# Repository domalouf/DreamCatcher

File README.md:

# DreamCatcher
 A react native mobile app for the DreamCatcher sleep mask

- `DreamCatcherAppNew/` - the app
- `arduino/` - mask firmware
- `hardware/` - PCB design for the mask ([details](hardware/README.md))

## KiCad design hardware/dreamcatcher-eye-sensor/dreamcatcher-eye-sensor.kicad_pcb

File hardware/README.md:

# DreamCatcher hardware

Two small boards that replace the ESP32 dev board and the QTR-1A breakout in the mask:

| Board | Size | What's on it |
| --- | --- | --- |
| [Main board](dreamcatcher-main) | 50 x 18 mm, 4 layers, parts on one side | ESP32-C3 module, USB-C charging and flashing, LiPo charger, 3.3 V regulator, accelerometer, two eye sensor connectors |
| [Eye sensor board](dreamcatcher-eye-sensor) (one per eye) | 8 x 9.5 mm, 2 layers | IR reflectance sensor and a red cue LED |

The main board sits on the forehead or temple. Each eye sensor board sits in front of an
eye and connects to the main board with a thin four-wire cable, so nothing bulky
presses on the eye.

**This design has not been built yet.** It passes an automated test suite (see
[What has been checked](#what-has-been-checked)), but no board has been manufactured or
powered. Read [Before you order](#before-you-order) first.

## How it works

```mermaid
flowchart LR
    USB[USB-C] --> CHG[MCP73831 charger<br/>100 mA]
    USB --> PATH[Power path<br/>Q1 + D1]
    CHG --> BAT[LiPo cell]
    BAT --> PATH
    PATH --> LDO[XC6220<br/>3.3 V]
    LDO --> MCU[ESP32-C3-MINI-1]
    USB <-- data --> MCU
    MCU -- I2C --> ACC[LIS2DH12<br/>accelerometer]
    MCU -- sensor power switch --> EYES
    MCU -- cue LED drive --> EYES[Left and right<br/>eye sensor boards]
    EYES -- analog --> MCU
    BAT -- divider --> MCU
```

- **Eye sensors.** Each eye board carries a QRE1113GR, the same sensor as on the QTR-1A
  you use now, wired the same way: a 220 Ω resistor for the IR LED and a 47 kΩ pull-up
  on the phototransistor. Those resistors are on the main board, so the eye board holds
  only the sensor and the cue LED. Q2 switches power to both sensors, so they draw
  nothing between readings.
- **Accelerometer.** A LIS2DH12 detects head and body movement directly, instead of
  inferring it from the IR signal. Its interrupt pin can wake the chip from deep sleep.
- **Power.** USB-C charges the cell at 100 mA. On USB the board runs from USB and the
  cell only charges (Q1 and D1), so charging finishes properly. The regulator draws
  about 8 µA itself.
- **USB.** The ESP32-C3's built-in USB serial/JTAG is wired to the connector, so the
  board is flashed over USB-C with no extra chip.

### Pin map

| ESP32-C3 pin | Net | Use |
| --- | --- | --- |
| GPIO0 (ADC1_CH0) | `EYE_L_OUT` | Left eye sensor reading |
| GPIO1 (ADC1_CH1) | `EYE_R_OUT` | Right eye sensor reading |
| GPIO2 | `SENS_EN_N` | Eye sensor power, **low = on** |
| GPIO3 (ADC1_CH3) | `VBAT_SENSE` | Battery voltage / 2 |
| GPIO4 | `ACC_INT1` | Accelerometer interrupt (can wake from deep sleep) |
| GPIO5 | `CUE_L` | Left cue LED, high = on |
| GPIO6 | `CUE_R` | Right cue LED, high = on |
| GPIO7 | `LED_STAT` | Green status LED on the main board, high = on |
| GPIO8 | `I2C_SDA` | Accelerometer (address 0x19) |
| GPIO10 | `I2C_SCL` | Accelerometer |
| GPIO9 | `BOOT` | BOOT pad |
| GPIO18 / GPIO19 | `USB_DM` / `USB_DP` | USB |
| GPIO20 / GPIO21 | `UART_RX` / `UART_TX` | Debug pads |

### Eye sensor cable

Both ends use the same order. The main board has a JST SH 4-pin socket (1 mm pitch) for
each eye; the eye board has four plated holes to solder the wires into.

| Pin | Signal |
| --- | --- |
| 1 | Cue LED anode |
| 2 | Ground |
| 3 | Phototransistor output |
| 4 | IR LED anode |

A ready-made "JST SH 4-pin to bare wire" cable works: plug one end into the main board
and solder the other to the eye board. These are the same plugs as Qwiic / STEMMA QT
cables, but the signals are not I2C, so don't plug a Qwiic device in.

## Before you order

1. **Pick the battery.** The charger is set to 100 mA (R3 = 10 kΩ), which suits a cell
   of 100 mAh or more. For another charge current use R3 = 1000 / amps. Use a cell with
   its own protection circuit (most pouch cells with leads have one); the board has no
   under-voltage cut-off of its own. The leads solder to the two pads marked + and −.
   There is no reverse-polarity protection, so check the lead colours against the
   markings before soldering.
2. **Look the boards over in KiCad.** The tracks were placed by a script, not by hand.
   They pass the design rule check, but they are not pretty, and a second pair of eyes
   on a first board is always worth it. The main board also has spare room: someone
   laying it out by hand could bring it down to roughly 45 x 18 mm.
3. **Check the parts in JLCPCB's parts list.** Stock changes daily. Things I noticed:
   - QRE1113GR (C232862) had low stock and one listing calls it not recommended for new
     designs. If it's unavailable, leave it off the order and solder sensors from
     Digi-Key or Mouser yourself.
   - ESP32-C3-MINI-1-N4 (C2838502) may be replaced by the newer ESP32-C3-MINI-1-N4X,
     which has the same footprint.
   - I could not confirm the green LED's part number (C72043).
4. **Check part rotation in JLCPCB's placement preview.** Their rotation convention
   differs from KiCad's for some packages (SOT-23, the USB connector, LEDs). Their
   preview shows each part on its pads; fix any that look turned.

### Ordering from JLCPCB

Each board folder has a `fab/` folder with what the order form asks for:

| File | Upload as |
| --- | --- |
| `*-gerbers.zip` | Gerber file |
| `*-bom.csv` | BOM (assembly step) |
| `*-cpl.csv` | CPL / pick-and-place file (assembly step) |

Settings that differ from the defaults:

| | Main board | Eye sensor board |
| --- | --- | --- |
| Layers | 4 | 2 |
| Thickness | 0.8 mm | 0.8 mm |
| Assembly side | Top | Top |

Both boards have parts on the top side only. The eye boards are tiny, so order them
panelised by JLCPCB if their minimum size for assembly requires it.

## Assembly notes

- **Board thickness with parts**: about 4.1 mm for the main board (0.8 mm board plus the
  USB-C connector at 3.3 mm; the module is 2.4 mm and the JST sockets 3 mm). The eye
  board is about 2.5 mm (0.8 mm board plus the 1.7 mm sensor).
- **Antenna.** The left 5.75 mm of the main board (under the module's antenna) has no
  copper. Keep the battery, wires and anything metal away from that end.
- **Sensor distance.** The QRE1113 works best 3-6 mm from the eyelid, as before.
- **Cue LED.** Each eye board has one. The firmware can drive either or both.
- **Buttons and pads.** RESET is a button. BOOT and GND are two pads next to it: bridge
  them with tweezers while pressing RESET to force the USB bootloader. This is only
  needed if the firmware crashes too early for a normal USB upload. The pads (3V3, TX,
  RX, BOOT, GND, BAT+, BAT-) are named on the back of the board.
- **Mounting.** The boards have no mounting holes; the case should hold them by the
  edges.

## Firmware changes

`arduino/DreamCatcher_v3` targets the classic ESP32 dev board. For this board:

- Build for **ESP32C3 Dev Module** with **USB CDC On Boot** enabled.
- Pins: sensor input 32 → 0 (left) and 1 (right), cue LED 26 → 5 and 6, status LED
  2 → 7.
- Sensor power was a pin driven high (27). It is now GPIO2 driven **low** to switch the
  sensors on.
- The ESP32-C3's ADC reads up to about 2.5 V, not 3.1 V. The sensor output can reach
  3.3 V when nothing reflects, which now reads as full scale. The existing "reading
  must not hit either end" check covers this.
- New: battery level on GPIO3 (reads half the battery voltage), and the accelerometer
  on I2C for body movement.
- Deep sleep on a timer works as before. To also wake on movement, use
  `esp_deep_sleep_enable_gpio_wakeup` on GPIO4.

## Power estimate

These are estimates from datasheet figures, not measurements.

| State | Current | Notes |
| --- | --- | --- |
| Deep sleep | about 20 µA | ESP32-C3 5 µA, regulator 8 µA, battery divider 2 µA, rest leakage |
| Dream window | 2-3 mA average | 25 readings a second, light sleep in between, both IR LEDs at 9.5 mA for about 1.5 ms per reading |
| Bluetooth advertising | 5-15 mA average | Depends on the advertising interval |

A 100-150 mAh cell should last several nights between charges.

## What has been checked

`tests/` holds about 70 automated checks that read the finished KiCad files and the
factory files. Run them from the `hardware` folder with KiCad's Python:

```bash
python3 -m unittest discover -s tests -v
```

| File | What it asks |
| --- | --- |
| `test_circuit.py` | Is the circuit right? Every chip powered from the correct supply and grounded, the processor's start-up pins set so it boots, USB data on the pins the chip uses for USB, sensor signals on pins that can measure voltage, charge current safe for a small cell, LED currents within what a pin can drive, nothing left dangling. |
| `test_eye_sensor.py` | Is the eye board wired correctly, and does each of its four wires land on the matching pin of the main board's sockets? |
| `test_layout.py` | Is the board laid out sensibly? KiCad's own design rule check passes with nothing unconnected, no copper or parts under the antenna on any layer, USB and eye sockets open at the board edge, capacitors within 5 mm of the pins they serve, an unbroken ground plane, track and hole sizes JLCPCB can make. |
| `test_fab.py` | Do the factory files match the design? Schematic and board agree pin for pin, every part appears once in the bill of materials with an order number, the placement list has every part at its real position, the Gerber archive has every layer. |
| `test_router.py` | Does the script that draws the tracks obey its own rules (keeps its distance, goes round obstacles, reports failure rather than crossing another track)? |

Writing these tests found three faults in the first version of the board, all now
fixed: the ground plane ran under the antenna on an inner layer, the regulator's ground
pin had no ground via nearby, and some vias sat within 0.05 mm of a solder pad.

To see whether the tests would notice a mistake, I put twelve deliberate ones into a
copy of the design (USB data lines swapped, a 1 A charge current, a sensor on a pin
that can't measure, a backwards LED, eye-board wires swapped, a forgotten ground pin
and so on). Every one made at least one test fail.

What the tests cannot tell you:

- Whether the facts they rely on are right. They encode pin functions and limits from
  the datasheets as I understand them; a misreading would pass its own test.
- Anything that needs a real board: radio range, noise on the eye sensor signal, battery
  life, whether the footprints fit the actual parts.
- KiCad's electrical rules check on the schematic, which KiCad 7's command line can't
  run. Open the schematic in KiCad and run it once (Inspect > Electrical Rules Checker).

## Files

| | |
| --- | --- |
| `dreamcatcher-main/`, `dreamcatcher-eye-sensor/` | KiCad projects (open the `.kicad_pro`), `fab/` outputs and `docs/` previews with the schematic as PDF |
| `lib/` | The project's own symbols and footprints |
| `scripts/` | Generates everything above |
| `tests/` | Checks on the generated design, see [What has been checked](#what-has-been-checked) |

The KiCad files are generated: parts, nets and placement live in
[`scripts/boards.py`](scripts/boards.py). You can edit the boards in KiCad directly, but
running the scripts again overwrites them. To regenerate (KiCad 7 or newer, plus
`rsvg-convert` for the preview images):

```bash
cd hardware/scripts
python3 build.py
```

Routing the main board takes several minutes. The schematics are drawn label-style: each
part stands alone and pins with the same label are connected.

The ESP32-C3-MINI-1 footprint is from
[Espressif's KiCad library](https://github.com/espressif/kicad-libraries) (CC-BY-SA 4.0
with an exception for designs that use it).

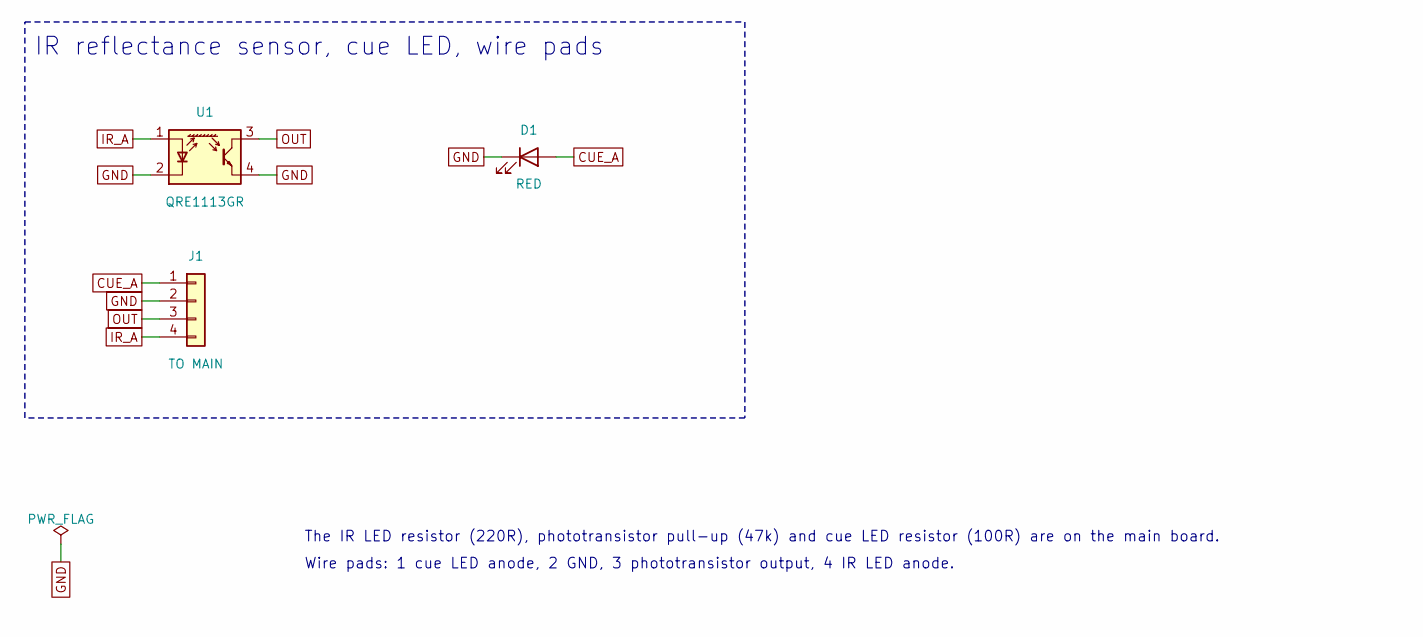
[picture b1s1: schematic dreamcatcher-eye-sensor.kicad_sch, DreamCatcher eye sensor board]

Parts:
D1: RED; LED_0603_1608Metric; MPN 0603 red LED; LCSC C2286
J1: TO MAIN; WirePads_1x04_P1.8mm
U1: QRE1113GR; OnSemi_CASE100CY; MPN QRE1113GR; LCSC C232862

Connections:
CUE_A: D1.2 (A), J1.1
GND: D1.1 (K), J1.2, U1.2 (K), U1.4
IR_A: J1.4, U1.1 (A)
OUT: J1.3, U1.3

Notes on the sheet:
IR reflectance sensor, cue LED, wire pads
The IR LED resistor (220R), phototransistor pull-up (47k) and cue LED resistor (100R) are on the main board.
Wire pads: 1 cue LED anode, 2 GND, 3 phototransistor output, 4 IR LED anode.

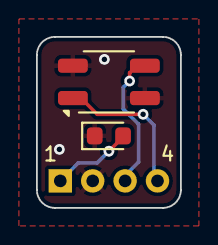
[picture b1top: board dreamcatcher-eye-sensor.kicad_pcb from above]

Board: 2 copper layers, 8.0 x 9.5 mm, 3 parts (0 on the bottom side), 4 nets.

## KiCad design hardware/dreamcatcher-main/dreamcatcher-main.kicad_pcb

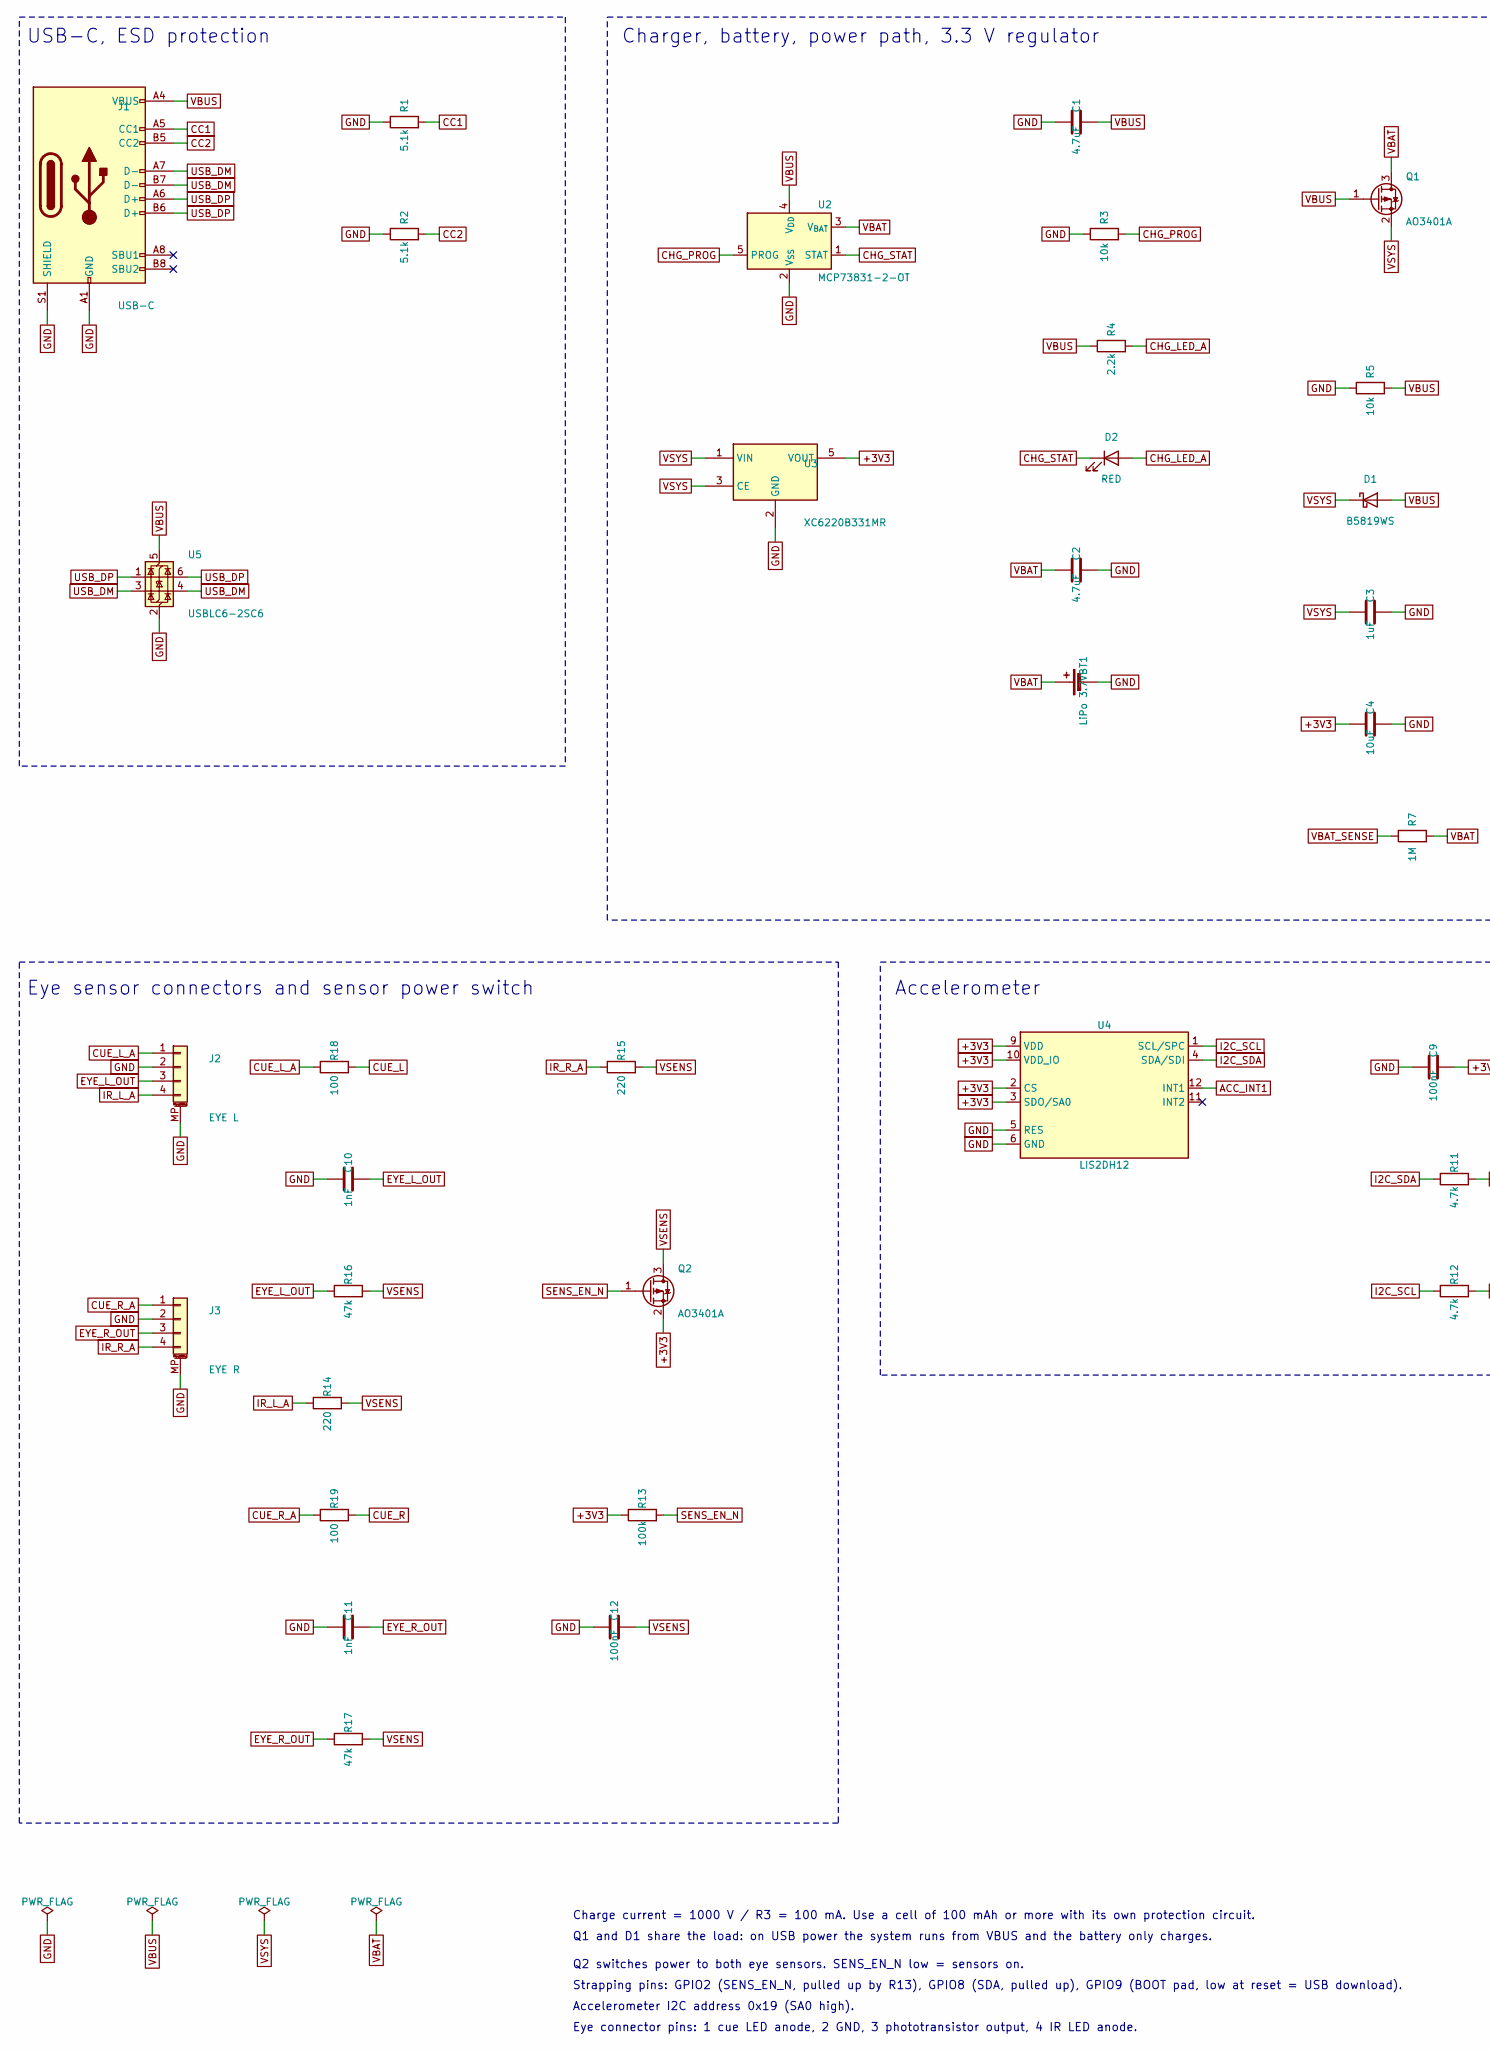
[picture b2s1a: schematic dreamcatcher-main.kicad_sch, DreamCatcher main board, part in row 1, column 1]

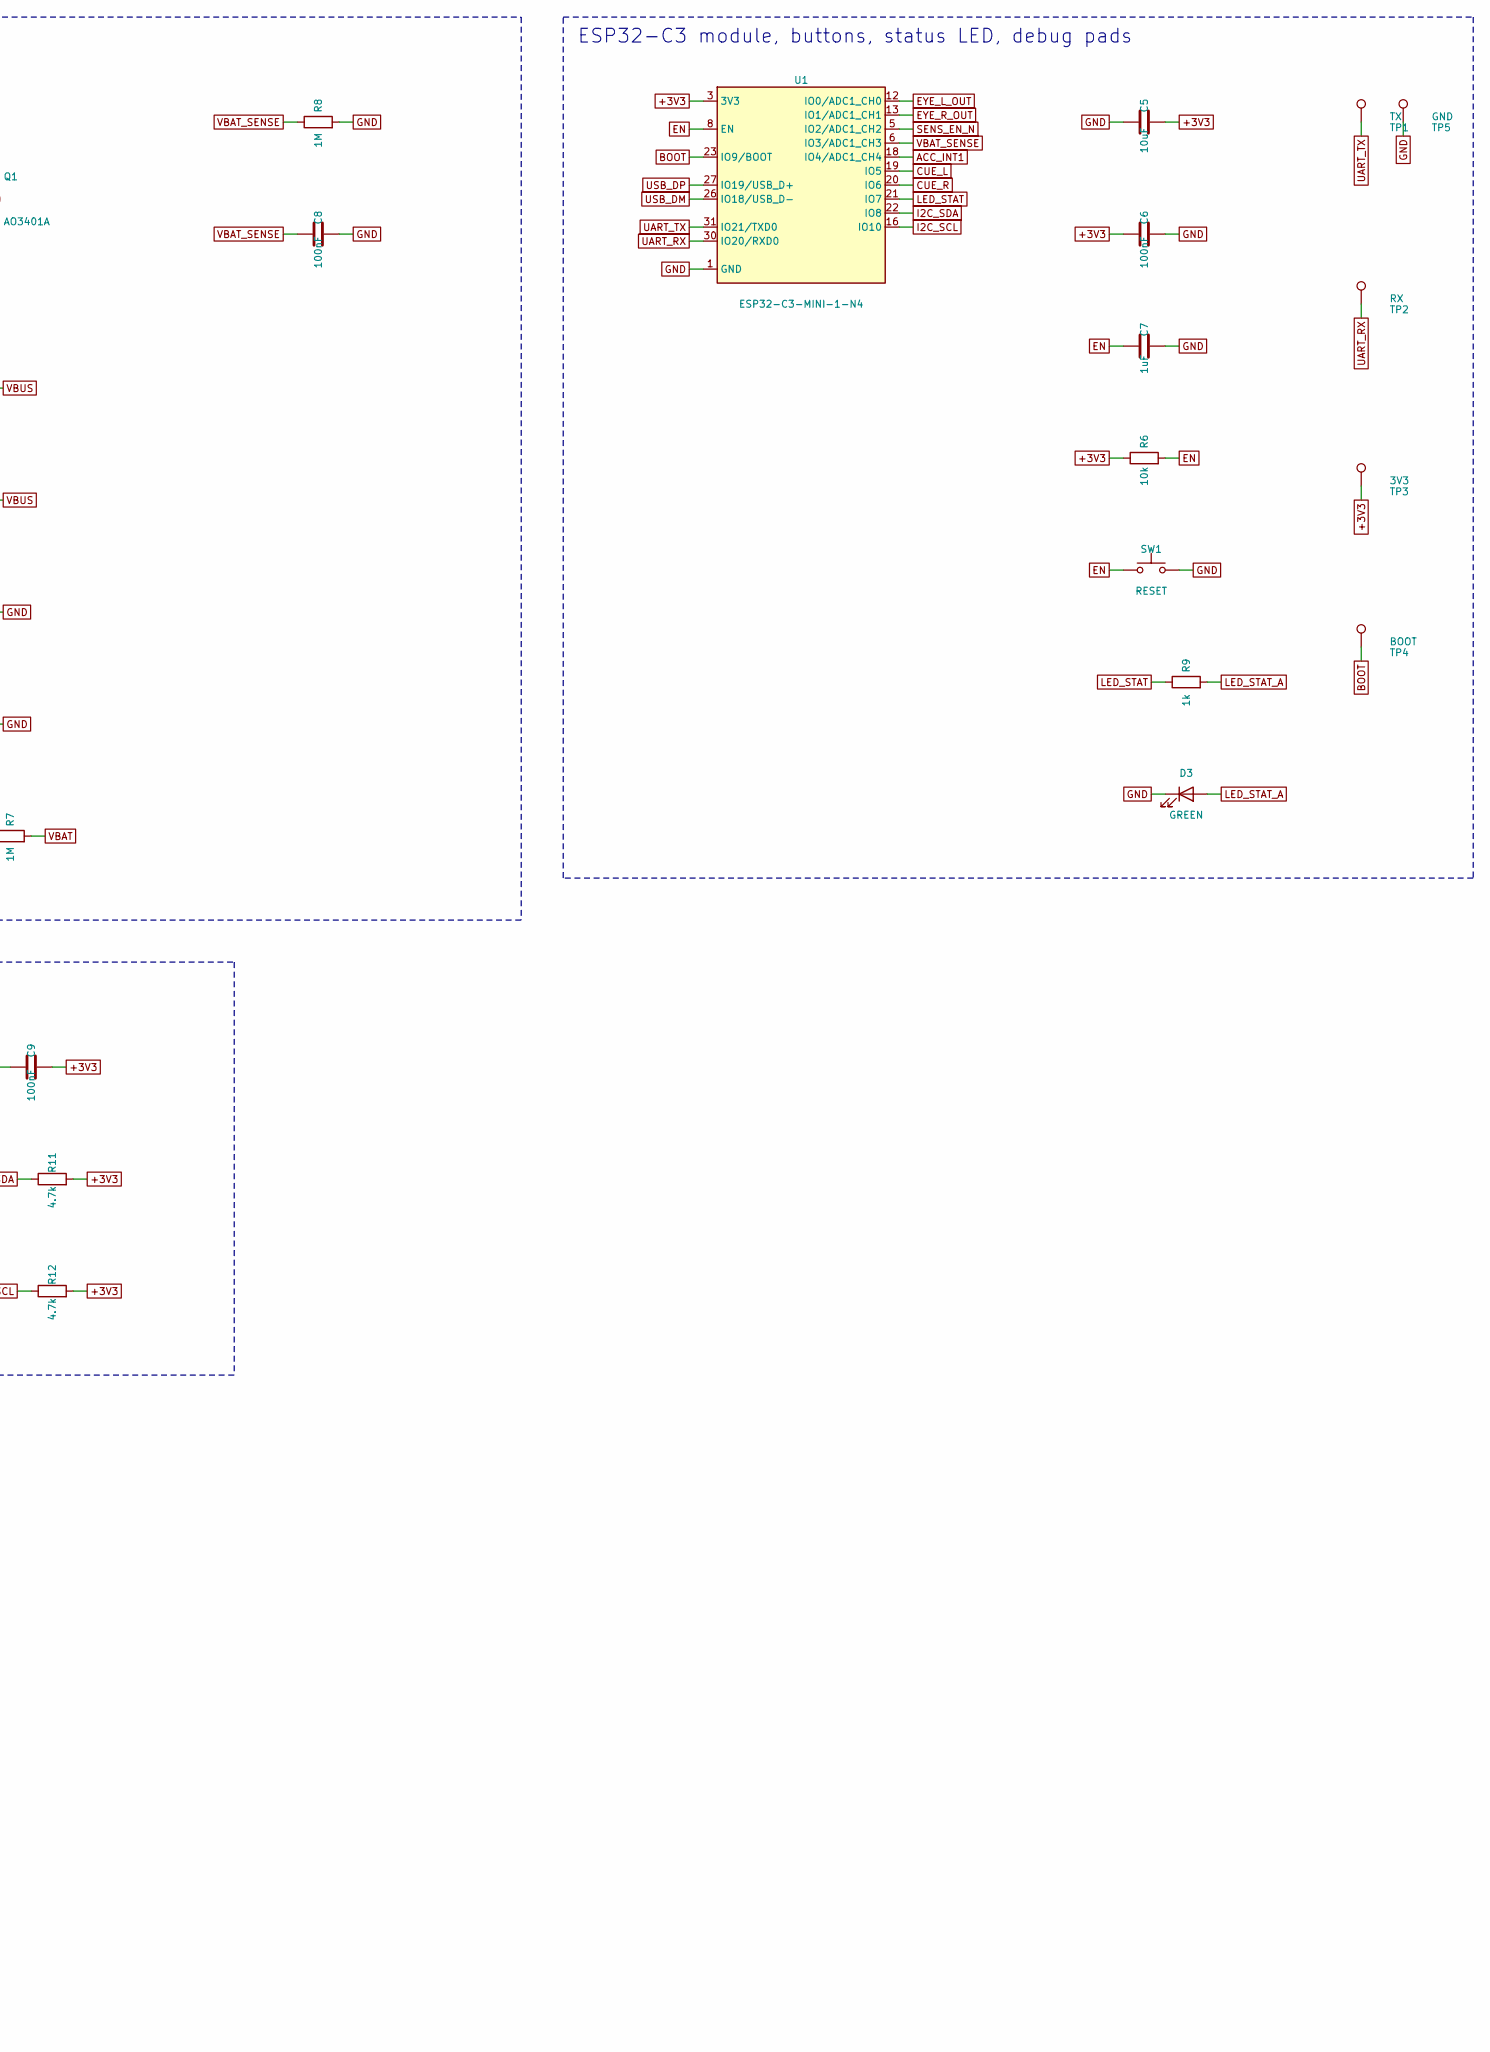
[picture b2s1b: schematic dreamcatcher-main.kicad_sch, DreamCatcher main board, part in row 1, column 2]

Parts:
BT1: LiPo 3.7V; BatteryPads_P3.6mm
C1, C2: 4.7uF; C_0603_1608Metric; MPN 0603 4.7uF X5R/X7R; LCSC C19666
C3, C7: 1uF; C_0402_1005Metric; MPN 0402 1uF X5R/X7R; LCSC C52923
C4, C5: 10uF; C_0603_1608Metric; MPN 0603 10uF X5R/X7R; LCSC C19702
C6, C8, C9, C12: 100nF; C_0402_1005Metric; MPN 0402 100nF X5R/X7R; LCSC C1525
C10, C11: 1nF; C_0402_1005Metric; MPN 0402 1nF X5R/X7R; LCSC C1523
D1: B5819WS; D_SOD-323; MPN B5819WS; LCSC C64886
D2: RED; LED_0603_1608Metric; MPN 0603 red LED; LCSC C2286
D3: GREEN; LED_0603_1608Metric; MPN 0603 green LED; LCSC C72043
J1: USB-C; USB_C_Receptacle_HRO_TYPE-C-31-M-12; MPN TYPE-C-31-M-12; LCSC C165948
J2: EYE L; JST_SH_SM04B-SRSS-TB_1x04-1MP_P1.00mm_Horizontal; MPN SM04B-SRSS-TB; LCSC C160404
J3: EYE R; JST_SH_SM04B-SRSS-TB_1x04-1MP_P1.00mm_Horizontal; MPN SM04B-SRSS-TB; LCSC C160404
Q1, Q2: AO3401A; SOT-23; MPN AO3401A; LCSC C15127
R1, R2: 5.1k; R_0402_1005Metric; MPN 0402 5.1k 1%; LCSC C25905
R3, R5, R6: 10k; R_0402_1005Metric; MPN 0402 10k 1%; LCSC C25744
R4: 2.2k; R_0402_1005Metric; MPN 0402 2.2k 1%; LCSC C25879
R7, R8: 1M; R_0402_1005Metric; MPN 0402 1M 1%; LCSC C26083
R9: 1k; R_0402_1005Metric; MPN 0402 1k 1%; LCSC C11702
R11, R12: 4.7k; R_0402_1005Metric; MPN 0402 4.7k 1%; LCSC C25900
R13: 100k; R_0402_1005Metric; MPN 0402 100k 1%; LCSC C25741
R14, R15: 220; R_0402_1005Metric; MPN 0402 220 1%; LCSC C25091
R16, R17: 47k; R_0402_1005Metric; MPN 0402 47k 1%; LCSC C25792
R18, R19: 100; R_0402_1005Metric; MPN 0402 100 1%; LCSC C25076
SW1: RESET; SW_SPST_B3U-1000P; MPN B3U-1000P; LCSC C231329
TP1: TX; TestPoint_Pad_D1.0mm
TP2: RX; TestPoint_Pad_D1.0mm
TP3: 3V3; TestPoint_Pad_D1.0mm
TP4: BOOT; TestPoint_Pad_D1.0mm
TP5: GND; TestPoint_Pad_D1.0mm
U1: ESP32-C3-MINI-1-N4; ESP32-C3-MINI-1; MPN ESP32-C3-MINI-1-N4; LCSC C2838502
U2: MCP73831-2-OT; SOT-23-5; MPN MCP73831T-2ACI/OT; LCSC C424093
U3: XC6220B331MR; SOT-23-5; MPN XC6220B331MR-G; LCSC C86534
U4: LIS2DH12; LGA-12_2x2mm_P0.5mm; MPN LIS2DH12TR; LCSC C110926
U5: USBLC6-2SC6; SOT-23-6; MPN USBLC6-2SC6; LCSC C7519

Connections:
+3V3: C4.1, C5.2, C6.1, C9.2, Q2.2 (S), R6.1, R11.2, R12.2, R13.1, TP3.1, U1.3 (3V3), U3.5 (VOUT), U4.2 (CS), U4.3 (SDO/SA0), U4.9 (VDD), U4.10 (VDD_IO)
ACC_INT1: U1.18 (IO4/ADC1_CH4), U4.12 (INT1)
BOOT: TP4.1, U1.23 (IO9/BOOT)
CC1: J1.A5 (CC1), R1.2
CC2: J1.B5 (CC2), R2.2
CHG_LED_A: D2.2 (A), R4.2
CHG_PROG: R3.2, U2.5 (PROG)
CHG_STAT: D2.1 (K), U2.1 (STAT)
CUE_L: R18.2, U1.19 (IO5)
CUE_L_A: J2.1, R18.1
CUE_R: R19.2, U1.20 (IO6)
CUE_R_A: J3.1, R19.1
EN: C7.1, R6.2, SW1.1, U1.8 (EN)
EYE_L_OUT: C10.2, J2.3, R16.1, U1.12 (IO0/ADC1_CH0)
EYE_R_OUT: C11.2, J3.3, R17.1, U1.13 (IO1/ADC1_CH1)
GND: BT1.2 (-), C1.1, C2.2, C3.2, C4.2, C5.1, C6.2, C7.2, C8.2, C9.1, C10.1, C11.1, C12.1, D3.1 (K), J1.A1 (GND), J1.A12 (GND), J1.B1 (GND), J1.B12 (GND), J1.S1 (SHIELD), J2.2, J2.MP (MountPin), J3.2, J3.MP (MountPin), R1.1, R2.1, R3.1, R5.1, R8.2, SW1.2, TP5.1, U1.1 (GND), U1.2, U1.11, U1.14, U1.36, U1.37, U1.38, U1.39, U1.40, U1.41, U1.42, U1.43, U1.44, U1.45, U1.46, U1.47, U1.48, U1.49, U1.50, U1.51, U1.52, U1.53, U2.2 (V_{SS}), U3.2 (GND), U4.5 (RES), U4.6 (GND), U4.7, U4.8, U5.2 (GND)
I2C_SCL: R12.1, U1.16 (IO10), U4.1 (SCL/SPC)
I2C_SDA: R11.1, U1.22 (IO8), U4.4 (SDA/SDI)
IR_L_A: J2.4, R14.1
IR_R_A: J3.4, R15.1
LED_STAT: R9.1, U1.21 (IO7)
LED_STAT_A: D3.2 (A), R9.2
SENS_EN_N: Q2.1 (G), R13.2, U1.5 (IO2/ADC1_CH2)
UART_RX: TP2.1, U1.30 (IO20/RXD0)
UART_TX: TP1.1, U1.31 (IO21/TXD0)
USB_DM: J1.A7 (D-), J1.B7 (D-), U1.26 (IO18/USB_D-), U5.3 (I/O2), U5.4 (I/O2)
USB_DP: J1.A6 (D+), J1.B6 (D+), U1.27 (IO19/USB_D+), U5.1 (I/O1), U5.6 (I/O1)
VBAT: BT1.1 (+), C2.1, Q1.3 (D), R7.2, U2.3 (V_{BAT})
VBAT_SENSE: C8.1, R7.1, R8.1, U1.6 (IO3/ADC1_CH3)
VBUS: C1.2, D1.2 (A), J1.A4 (VBUS), J1.A9 (VBUS), J1.B4 (VBUS), J1.B9 (VBUS), Q1.1 (G), R4.1, R5.2, U2.4 (V_{DD}), U5.5 (VBUS)
VSENS: C12.2, Q2.3 (D), R14.2, R15.2, R16.2, R17.2
VSYS: C3.1, D1.1 (K), Q1.2 (S), U3.1 (VIN), U3.3 (CE)

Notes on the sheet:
USB-C, ESD protection
Charger, battery, power path, 3.3 V regulator
ESP32-C3 module, buttons, status LED, debug pads
Eye sensor connectors and sensor power switch
Accelerometer
Charge current = 1000 V / R3 = 100 mA. Use a cell of 100 mAh or more with its own protection circuit.
Q1 and D1 share the load: on USB power the system runs from VBUS and the battery only charges.
Q2 switches power to both eye sensors. SENS_EN_N low = sensors on.
Strapping pins: GPIO2 (SENS_EN_N, pulled up by R13), GPIO8 (SDA, pulled up), GPIO9 (BOOT pad, low at reset = USB download).
Accelerometer I2C address 0x19 (SA0 high).
Eye connector pins: 1 cue LED anode, 2 GND, 3 phototransistor output, 4 IR LED anode.

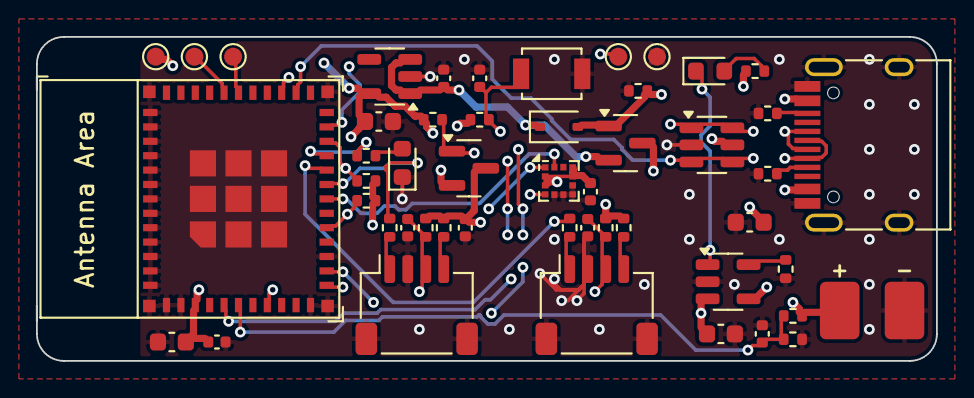
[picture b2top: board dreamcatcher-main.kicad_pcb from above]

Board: 4 copper layers, 50.0 x 18.0 mm, 50 parts (0 on the bottom side), 32 nets.

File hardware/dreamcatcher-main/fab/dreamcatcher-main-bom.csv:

Comment,Designator,Footprint,MPN,LCSC Part #
4.7uF,"C1,C2",C_0603_1608Metric,0603 4.7uF X5R/X7R,C19666
1nF,"C10,C11",C_0402_1005Metric,0402 1nF X5R/X7R,C1523
10uF,"C5,C4",C_0603_1608Metric,0603 10uF X5R/X7R,C19702
100nF,"C6,C8,C12,C9",C_0402_1005Metric,0402 100nF X5R/X7R,C1525
1uF,"C7,C3",C_0402_1005Metric,0402 1uF X5R/X7R,C52923
B5819WS,D1,D_SOD-323,B5819WS,C64886
RED,D2,LED_0603_1608Metric,0603 red LED,C2286
GREEN,D3,LED_0603_1608Metric,0603 green LED,C72043
USB-C,J1,USB_C_Receptacle_HRO_TYPE-C-31-M-12,TYPE-C-31-M-12,C165948
EYE L,J2,JST_SH_SM04B-SRSS-TB_1x04-1MP_P1.00mm_Horizontal,SM04B-SRSS-TB,C160404
EYE R,J3,JST_SH_SM04B-SRSS-TB_1x04-1MP_P1.00mm_Horizontal,SM04B-SRSS-TB,C160404
AO3401A,"Q1,Q2",SOT-23,AO3401A,C15127
5.1k,"R1,R2",R_0402_1005Metric,0402 5.1k 1%,C25905
4.7k,"R11,R12",R_0402_1005Metric,0402 4.7k 1%,C25900
100k,R13,R_0402_1005Metric,0402 100k 1%,C25741
220,"R14,R15",R_0402_1005Metric,0402 220 1%,C25091
47k,"R16,R17",R_0402_1005Metric,0402 47k 1%,C25792
100,"R18,R19",R_0402_1005Metric,0402 100 1%,C25076
2.2k,R4,R_0402_1005Metric,0402 2.2k 1%,C25879
10k,"R6,R3,R5",R_0402_1005Metric,0402 10k 1%,C25744
1M,"R7,R8",R_0402_1005Metric,0402 1M 1%,C26083
1k,R9,R_0402_1005Metric,0402 1k 1%,C11702
RESET,SW1,SW_SPST_B3U-1000P,B3U-1000P,C231329
ESP32-C3-MINI-1-N4,U1,ESP32-C3-MINI-1,ESP32-C3-MINI-1-N4,C2838502
MCP73831-2-OT,U2,SOT-23-5,MCP73831T-2ACI/OT,C424093
XC6220B331MR,U3,SOT-23-5,XC6220B331MR-G,C86534
LIS2DH12,U4,LGA-12_2x2mm_P0.5mm,LIS2DH12TR,C110926
USBLC6-2SC6,U5,SOT-23-6,USBLC6-2SC6,C7519

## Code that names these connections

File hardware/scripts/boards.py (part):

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    Part("U1", "ESP32-C3-MINI-1-N4", "DreamCatcher:ESP32-C3-MINI-1", "DreamCatcher:ESP32-C3-MINI-1",
         {**{n: "GND" for n in ESP_GND},
          "3": "+3V3", "8": "EN",
          "12": "EYE_L_OUT",    # GPIO0 / ADC1_CH0
          "13": "EYE_R_OUT",    # GPIO1 / ADC1_CH1
          "5": "SENS_EN_N",     # GPIO2 (strapping pin, held high at boot by R13)
          "6": "VBAT_SENSE",    # GPIO3 / ADC1_CH3
          "18": "ACC_INT1",     # GPIO4 (can wake the chip from deep sleep)
          "19": "CUE_L",        # GPIO5
          "20": "CUE_R",        # GPIO6
          "21": "LED_STAT",     # GPIO7
          "22": "I2C_SDA",      # GPIO8 (strapping pin, pulled up by the I2C resistor)
          "23": "BOOT",         # GPIO9 (strapping pin, low at reset = download mode)
          "16": "I2C_SCL",      # GPIO10
          "26": "USB_DM",       # GPIO18
          "27": "USB_DP",       # GPIO19
          "30": "UART_RX",      # GPIO20
          "31": "UART_TX"},     # GPIO21
         (8.5, 9.0, 90), "ESP32-C3-MINI-1-N4", "C2838502", "mcu"),
    C("C5", "10uF", "GND", "+3V3", (7.5, 16.95, 0), "C19702", "mcu", FP_C0603),
    C("C6", "100nF", "+3V3", "GND", (10.0, 16.95, 0), "C1525", "mcu"),
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
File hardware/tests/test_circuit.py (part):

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        self.assertEqual(d.pin("U4", "VDD"), "+3V3")
        self.assertEqual(d.pin("U4", "VDD_IO"), "+3V3")
        self.assertEqual(d.pin("U3", "VOUT"), "+3V3")
        self.assertEqual(d.pin("U3", "VIN"), "VSYS")
        self.assertEqual(d.pin("U2", "V_{DD}"), "VBUS")
        self.assertEqual(d.pin("U2", "V_{BAT}"), "VBAT")
        self.assertEqual(d.pin("U5", "VBUS"), "VBUS")
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        d = self.d
        self.assertEqual(d.kind["Q1"], "Q_PMOS_GSD")
        self.assertEqual(d.pin("Q1", "G"), "VBUS")
        self.assertEqual(d.pin("Q1", "S"), "VSYS")
        self.assertEqual(d.pin("Q1", "D"), "VBAT")
        self.assertEqual(d.pin("D1", "A"), "VBUS")
        self.assertEqual(d.pin("D1", "K"), "VSYS")
        pull_downs = d.between("R", "VBUS", "GND")
        self.assertEqual(len(pull_downs), 1, "Q1's gate needs pulling low when USB is unplugged")
        self.assertLessEqual(d.ohms(pull_downs[0]), 100e3)
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        self.assertGreater(full_battery, 1.0, "divides so far down that resolution is wasted")
        microamps = 4.2 / (r_top + r_bottom) * 1e6
        self.assertLess(microamps, 5, "the divider is always connected, so it must draw very little")
        self.assertTrue(d.between("C", "VBAT_SENSE", "GND"), "a high-value divider needs a capacitor at the ADC pin")

    def test_charge_led_lights_while_charging(self):
        # STAT pulls low while charging, so the LED sits between USB power and STAT
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        d = self.d
        self.assertEqual(d.kind["Q2"], "Q_PMOS_GSD")
        self.assertEqual(d.pin("Q2", "S"), "+3V3")
        self.assertEqual(d.pin("Q2", "D"), "VSENS")
        gate = d.pin("Q2", "G")
        self.assertTrue(d.between("R", gate, "+3V3"), "the gate needs a pull-up so the switch starts off")
        d.gpio(gate)
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        d = self.d
        for side, connector in (("L", "J2"), ("R", "J3")):
            with self.subTest(eye=side):
                infrared = d.between("R", "VSENS", d.pin(connector, "Pin_4"))
                self.assertEqual(len(infrared), 1)
                milliamps = (SUPPLY - 1.2) / d.ohms(infrared[0]) * 1000
                self.assertTrue(5 <= milliamps <= 20, f"IR LED current {milliamps:.1f} mA")
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
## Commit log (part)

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2024-04-02 React Native Init
    Followed instructions from: https://reactnative.dev/docs/environment-setup
2024-04-07 Added bottom tab navigation
    Got react-native-vector-icons to work
2024-04-07 Added Tab Navigation
    Made basic screens, added blur effect to tab navigation bar
2024-04-08 Added BLE functions to dreamcatcher page
    Added a bunch of functions to the DCSCreen.tsx file, all from https://blog.logrocket.com/using-react-native-ble-manager-mobile-app/
2024-04-15 Working on dream catcher page
2024-04-20 Changing esp32 communication
2024-04-21 Added settings screen and time picker
2024-04-22 Added icons and release bundle gradle stuff
2024-04-22 Trying to get bundle working
2024-04-22 Switched icons back, I think this is a working state
2024-04-22 Added new icons
2024-05-03 Added new connection page
    Added page to connect to sleep mask before accessing the controls
2024-10-06 addition by subtraction
2025-12-20 Initialize project with React dependency
    Add .gitignore to exclude node_modules and set up package.json with React 19.2.3 as a dependency.
2025-12-21 Got app to run on mac
    The iPhone emulator works
2025-12-21 Made new folder for updated app
    All the old react native dependencies were in the way, so I made a new react native project and just moved the src and App files over
2025-12-21 Add DreamCatcherAppNew app to runOnWindows branch
2025-12-21 Add DreamCatcherAppNew as regular folder (not submodule)
2025-12-21 changed font package
    The old import was throwing an error
2025-12-21 Changed date time picker
    The old date time picker package wasn't good I guess
2025-12-31 Convert JournalScreen to TypeScript and add entry features
    Replaces JournalScreen.js with JournalScreen.tsx, migrating the screen to TypeScript and adding new features: users can now add, view, and delete dream entries with modals for entry creation and deta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
2025-12-31 Updated UI
    Changed basic look of main screens' UI
2025-12-31 Removed old dreamcatcher app
    I'm deleting the old version of the app. I haven't tried to use the bluetooth functionality that worked on the old version. If it doesn't work on the new one I'll just cry.
2025-12-31 Small UI update
    changed colors a little bit
2025-12-31 Added async storage
    The dream journal saves to the local storage
2025-12-31 Added cool picture
    Looks cool
2026-01-01 Changed UI
    little changes
2026-01-02 Added old arduino files
    Some of these might still work hopefully, probably not
2026-01-04 Fixed android bluetooth permissions
    added android bluetooth permissions
2026-01-04 Adding bluetooth to app
    Trying to blend esp32 and app together harmoninousoloy
2026-01-04 idk mane
    pain
2026-01-04 bruh
2026-01-04 got ESP32 to show up on bluetooth scan
    we are so back
2026-01-04 Hid the nav bar
    Moved the android navigation bar on the bottom of the screen away
2026-01-07 Consolidated connect screen
    The connect screen does everything the old DC screen did, the UI to control the esp32 pops up after the connection is made
2026-01-13 Added TODO list
2026-01-13 Moved arduino files
2026-01-15 Added esp32 storage check
    Basic program to check storage and ram of esp32
2026-01-19 Added IR sensor function to app
    The mobile app can trigger an IR sensing session
2026-01-19 Started sending from esp32
    The mobile app receives small data from esp32, now I need to show the IR scanning data
2026-01-19 Graph works
    I'm the goat fr
2026-01-19 Added real time data transfer
    The IR sensor works in real-time
2026-01-19 Cleaned up IR graph
    Graph looks a little better
2026-01-22 Added TODO's
    will start a new branch and work on them
2026-02-01 Send storage/ram data
2026-02-01 fixed storage and ram debugging transfer
2026-02-01 BLE connection is smoother
    The esp32 and smartphone remember each other so the ble connection is a little better
2026-02-01 Attempting to add dream window
    In the middle of getting the IR sensor to scan and find REM sleep, not working rn
2026-02-07 Added demo mode
    Still need to test it out
2026-02-08 QTR graph only shows 4 seconds
    The test graph now only shows 4 seconds of points so that it doesn't slow down trying to re-render 8+ seconds worth of points
2026-02-08 Removed demo function
    The qtr graph already did the same thing pretty much, just need to detect motion
2026-02-08 Revert "QTR graph only shows 4 seconds"
    This reverts commit 060005ab9ce2000f7f5c4045a12a42608bf1dafd.
2026-02-08 Revert "Removed demo function"
    This reverts commit 1c4d17a3630e10c99e07af9a9a386cf56f5d2f73.
2026-02-08 IR graph displays movement
    The phone logic detects movement, going to try to make the esp32 detect it
